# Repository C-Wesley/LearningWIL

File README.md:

# LearningWIL

**Water Is Life (WIL)** is an Autonomous Surface Vehicle (ASV) developed for Augusta Utilities as part of an internship collaboration with Augusta University.

This repository serves as a learning and continuation guide for future developers. It documents the programming, electronics, and system architecture required to understand and extend WIL.

## Project Overview

WIL is designed for environmental data collection and autonomous navigation of local waterways. Development spans embedded programming, sensor integration, data logging, and vehicle controls.

## Repository Structure

### 1. Beginner Examples
`Beginner Examples/`

This is the recommended starting point for new contributors.

- Build circuits 
- Type the code (do not copy–paste)
- Learn how each sensor works in isolation

Suggested exercises:
- Move the IMU and visualize data using the **Arduino Serial Plotter**
- Observe GPS latitude/longitude changes while stationary vs. moving
- Combine GPS, heading, and SD card logging into a simple data logger!

These examples are for you to better understand each sensor individually before trying to throw all of them together. 
They are the 'building blocks' so to speak of WIL. 

### 2. Class-Based Examples
`Class Based Examples/`

These examples introduce **Object-Oriented Programming (OOP)** in C++.

Example:
```cpp
File myFile = ...
```
This creates a `File` object, which:

- Encapsulates data related to files
- Provides methods (functions) that operate on that data

Using classes helps:

- Organize complex systems
- Isolate bugs
- Scale the codebase as features grow

### 3. Notebooks
`Notebooks/`

This directory contains a digital copy of the lab notebooks for WIL. Not every entry is directly related to WIL. Some were more for my own learning. However, there are several useful entries to help you get more familiar with WIL. In the Beginner Examples, I've linked the related entires on each sensors readme file.

### 4. WIL Development Code

`WILDev/`

This directory contains the arudino code running on:

- WIL (Arduino Giga)
- The remote controller (MKR 1310)

Subdirectories:

- `new code/` – current class-based implementation
- `old code/` – old version (no classes)

New development should be based on `new code/`.

## System Architecture

WIL is generally structured around the following diagrams.

 **:TODO:** Update class diagram to reflect latest architecture.

### Class Diagram

### Block Diagram

## Contributing

This repository is designed to be learned from, modified, and extended. Developers are encouraged to:

- Experiment
- Break things
- Document findings
- Improve clarity for the next developer

Water is life (and so is maintainable code).

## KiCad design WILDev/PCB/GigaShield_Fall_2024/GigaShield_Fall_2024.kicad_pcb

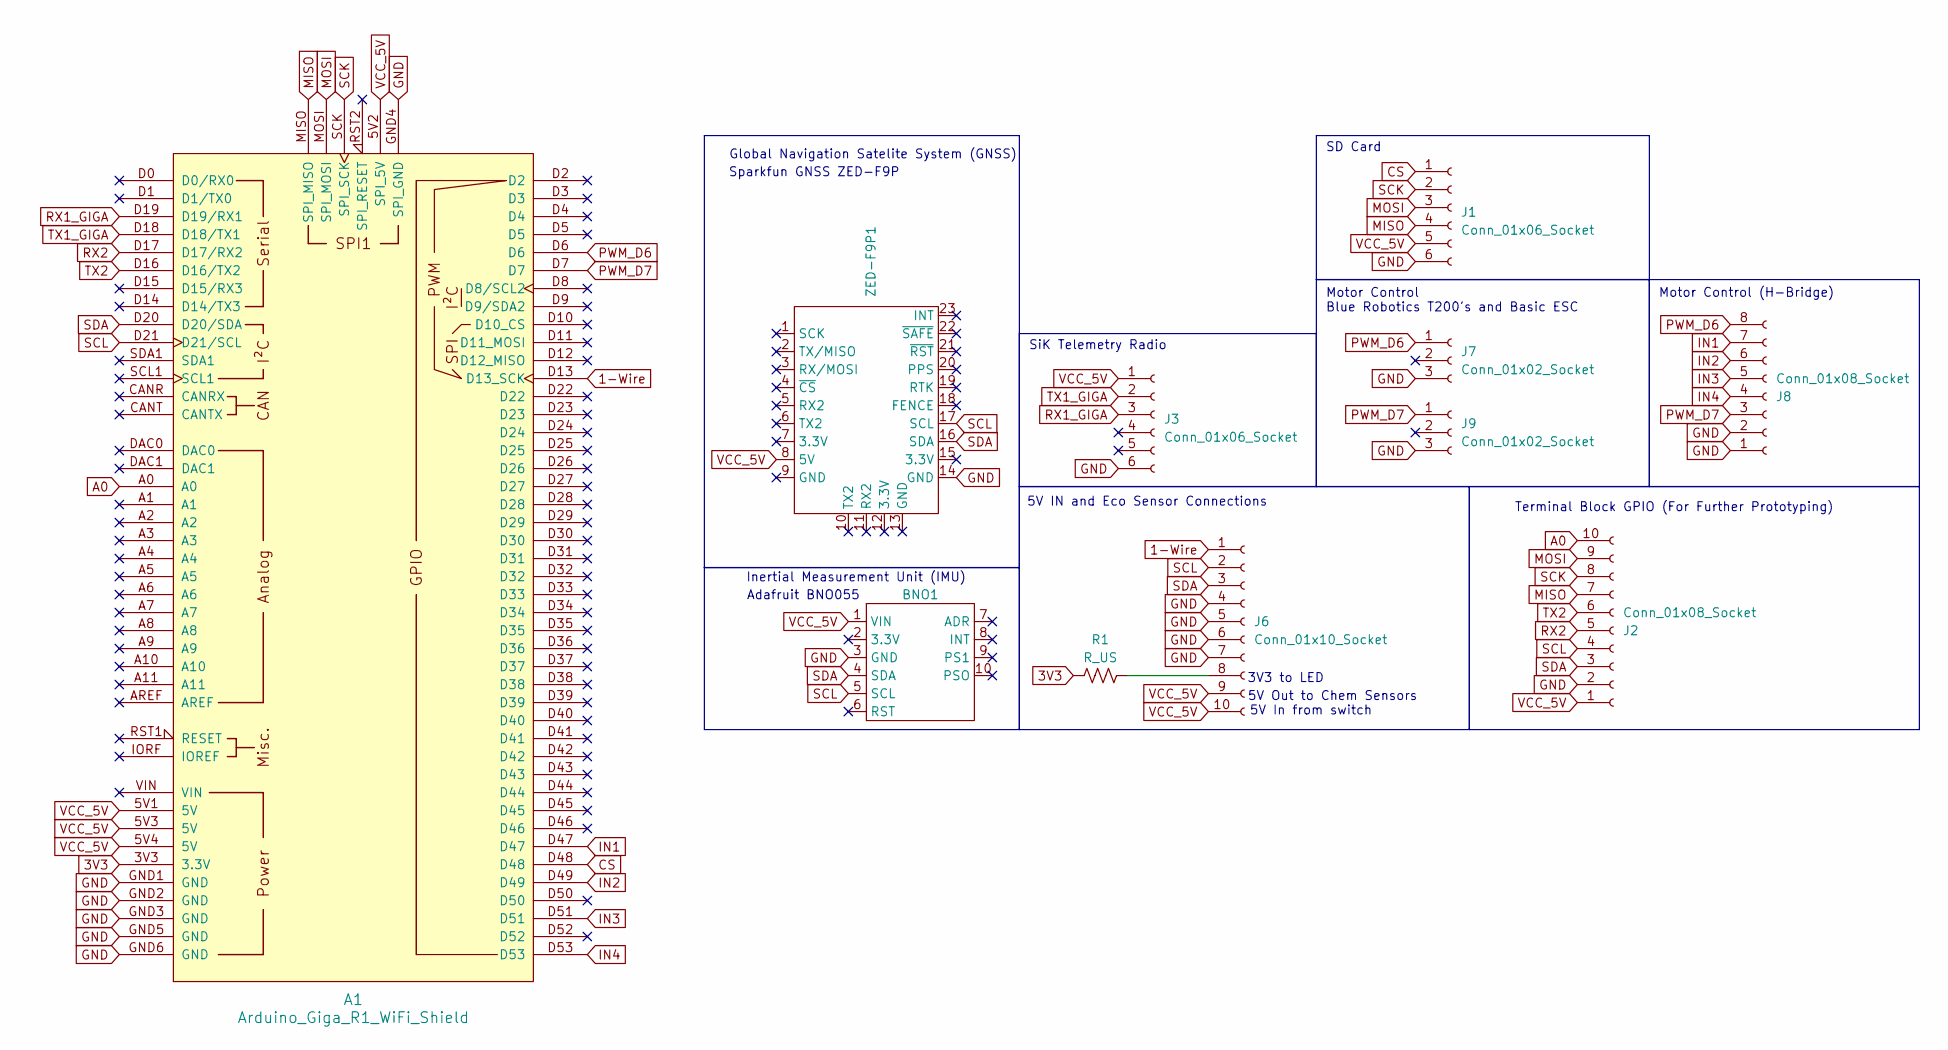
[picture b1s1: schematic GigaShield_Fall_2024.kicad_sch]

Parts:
A1: Arduino_Giga_R1_WiFi_Shield
BNO1: BNOAdafruit
J1: Conn_01x06_Socket; PinSocket_1x06_P2.54mm_Vertical
J2: Conn_01x08_Socket; TerminalBlock_Xinya_XY308-2.54-10P_1x10_P2.54mm_Horizontal
J3: Conn_01x06_Socket; JST_GH_SM06B-GHS-TB_1x06-1MP_P1.25mm_Horizontal
J6: Conn_01x10_Socket; TerminalBlock_Xinya_XY308-2.54-10P_1x10_P2.54mm_Horizontal
J7, J9: Conn_01x02_Socket; PinHeader_1x03_P2.54mm_Vertical
J8: Conn_01x08_Socket; TerminalBlock_Xinya_XY308-2.54-8P_1x08_P2.54mm_Horizontal
R1: R_US; R_Axial_DIN0309_L9.0mm_D3.2mm_P12.70mm_Horizontal
ZED-F9P1: SparkfunZedF9P

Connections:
1-Wire: A1.D13 (D13_SCK), J6.1
3V3: A1.3V3 (3.3V), R1.1
A0: A1.A0, J2.10
CS: A1.D48, J1.1
GND: A1.GND1 (GND), A1.GND2 (GND), A1.GND3 (GND), A1.GND4 (SPI_GND), A1.GND5 (GND), A1.GND6 (GND), BNO1.3 (GND), J1.6, J2.2, J3.6, J6.4, J6.5, J6.6, J6.7, J7.3, J8.1, J8.2, J9.3, ZED-F9P1.14 (GND)
IN1: A1.D47, J8.7
IN2: A1.D49, J8.6
IN3: A1.D51, J8.5
IN4: A1.D53, J8.4
MISO: A1.MISO (SPI_MISO), J1.4, J2.7
MOSI: A1.MOSI (SPI_MOSI), J1.3, J2.9
unnamed: J6.8, R1.2
PWM_D6: A1.D6, J7.1, J8.8
PWM_D7: A1.D7, J8.3, J9.1
RX1_GIGA: A1.D19 (D19/RX1), J3.3
RX2: A1.D17 (D17/RX2), J2.5
SCK: A1.SCK (SPI_SCK), J1.2, J2.8
SCL: A1.D21 (D21/SCL), BNO1.5 (SCL), J2.4, J6.2, ZED-F9P1.17 (SCL)
SDA: A1.D20 (D20/SDA), BNO1.4 (SDA), J2.3, J6.3, ZED-F9P1.16 (SDA)
TX1_GIGA: A1.D18 (D18/TX1), J3.2
TX2: A1.D16 (D16/TX2), J2.6
VCC_5V: A1.5V1 (5V), A1.5V2 (SPI_5V), A1.5V3 (5V), A1.5V4 (5V), BNO1.1 (VIN), J1.5, J2.1, J3.1, J6.9, J6.10, ZED-F9P1.8 (5V)

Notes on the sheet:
3V3 to LED
Sparkfun GNSS ZED-F9P
Terminal Block GPIO (For Further Prototyping)
5V Out to Chem Sensors
5V In from switch
5V IN and Eco Sensor Connections
Inertial Measurement Unit (IMU)
SiK Telemetry Radio
Motor Control (H-Bridge)
Adafruit BNO055
SD Card
Global Navigation Satelite System (GNSS)
Motor Control Blue Robotics T200's and Basic ESC

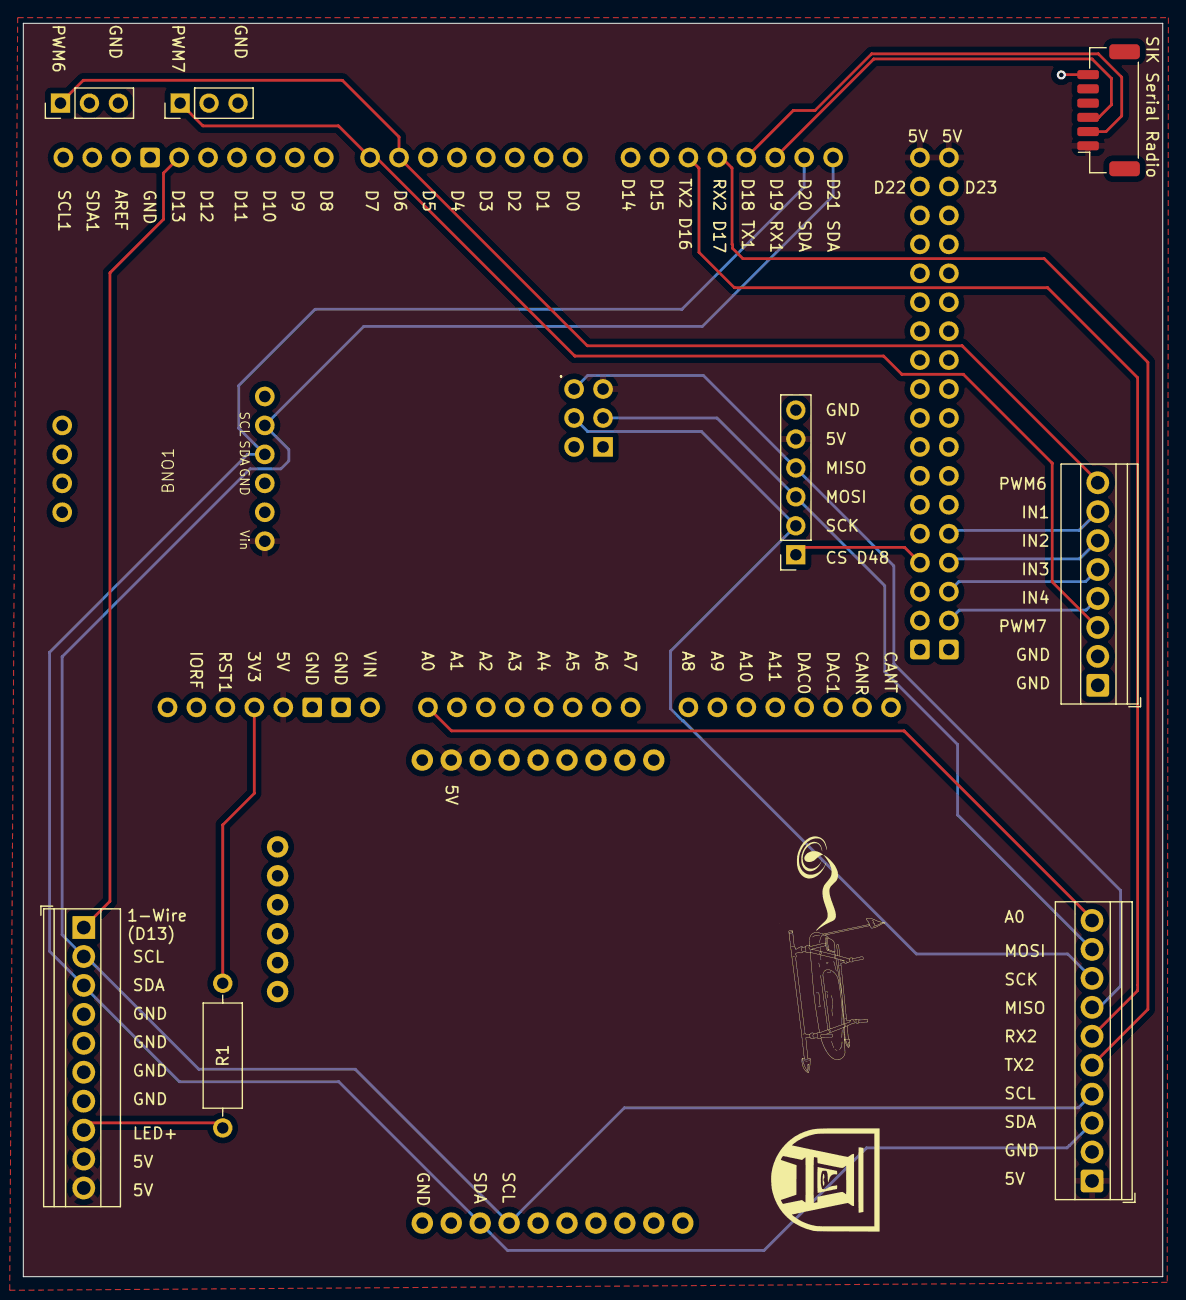
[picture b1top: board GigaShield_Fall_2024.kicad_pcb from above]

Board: 2 copper layers, 100.0 x 110.0 mm, 11 parts (0 on the bottom side), 22 nets.

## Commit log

2025-02-02 Adding SD Card Examples
2025-02-02 Rename README_SD.md to README.md
2025-02-02 Rename new_sd_circuit.jpg to sd_circuit.jpg
2025-12-24 Updating Repo Code
2025-12-24 Updating Readme with photos :)
2025-12-24 Updating Pics in readme
2025-12-24 Updating read me again
2025-12-24 Updating readme
2025-12-25 Adding Class Examples Read me
2025-12-25 Updating Class Examples Readme
2025-12-25 Fixing formating readme
2025-12-25 fixing table formating
2025-12-25 fixing table formatting
2025-12-26 Updating Read me
2025-12-26 Fixing picture links
2025-12-26 Fixing typo readme
2025-12-27 Updating PCB Files
2025-12-27 Updating gps readme
2025-12-27 Updated IMU readme
2025-12-27 Updating motor readme
2025-12-29 Updating SD Readme
2025-12-30 Updating radio read me
2025-12-30 Updating Sensors Readme
2026-01-09 Adding Notebook 1
2026-01-09 Removing Large file
2026-01-09 Adding Lab Notebook entries
2026-01-09 Adding Notebook 2
2026-01-11 updating BegEx.
2026-01-11 Adding new example code
2026-01-11 Adding new GPS Example
2026-01-11 Updating Readme's
2026-01-11 Fixing notebook issues
2026-05-18 Fixing bug in blinky debuging
2026-05-18 Adding URFA Data
2026-05-18 Adding QGIS Scripts
